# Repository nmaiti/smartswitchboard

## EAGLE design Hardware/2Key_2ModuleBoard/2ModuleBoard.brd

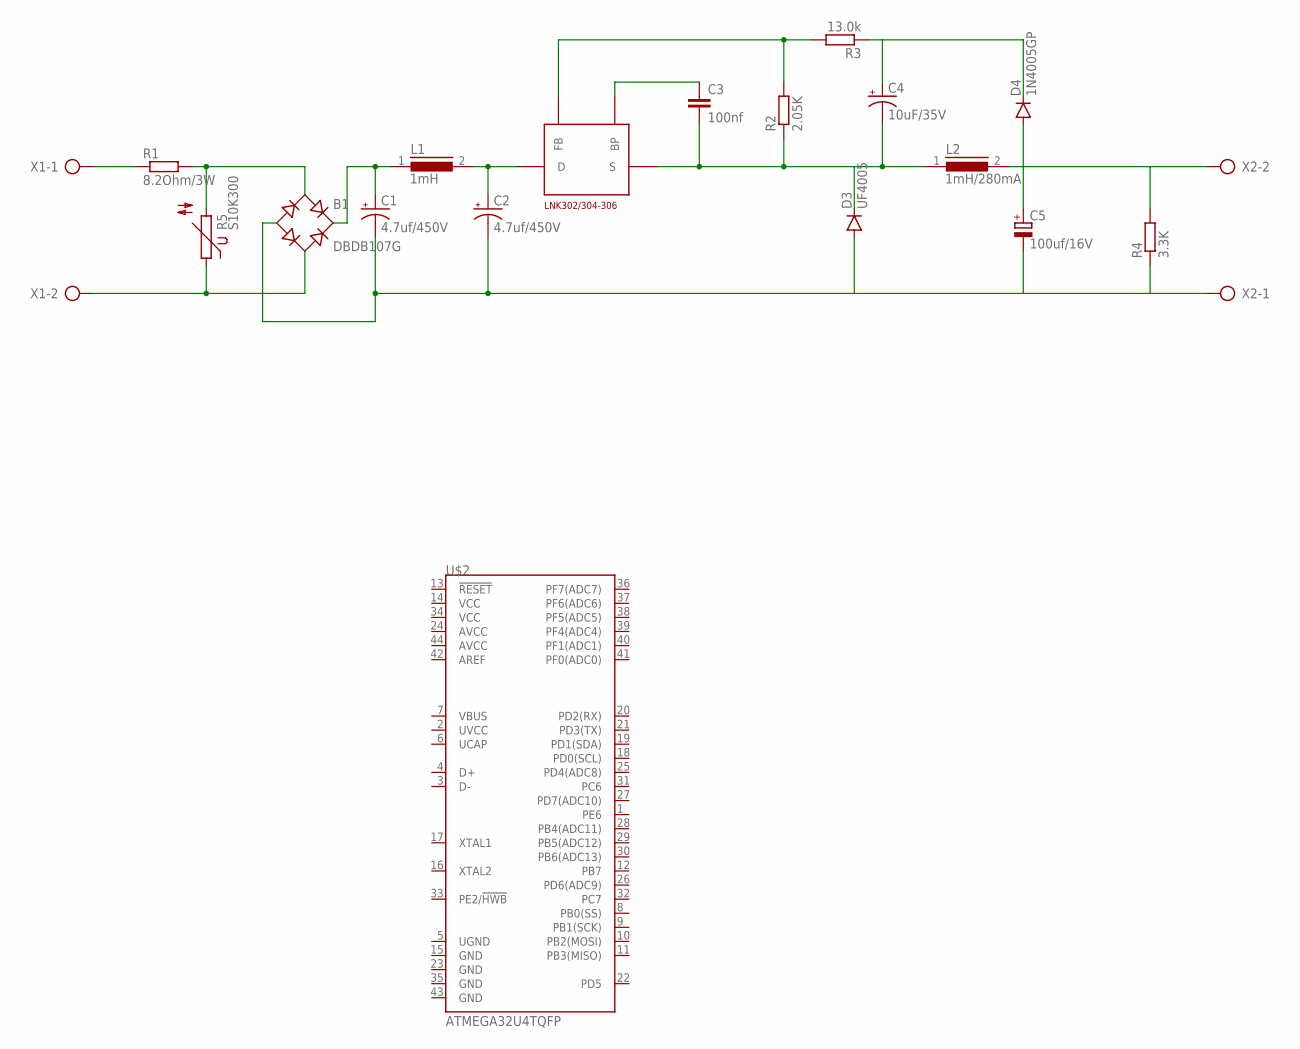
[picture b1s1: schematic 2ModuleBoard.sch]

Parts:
B1: DBDB107G; DB
C1, C2: 4.7uf/450V; CPOL-RADIAL-1000UF-25V-KIT
C3: 100nf; C2.5-4
C4: 10uF/35V; EIA3216
C5: 100uf/16V; E2,5-7
D3: UF4005; DIODE-1N4148-KIT
D4: 1N4005GP; DIODE-1N4148-KIT
L1: 1mH; 82114R
L2: 1mH/280mA; 82114R
R1: 8.2Ohm/3W; 0411/15
R2: 2.05K; M1206
R3: 13.0k; M1206
R4: 3.3K; M1206
R5: S10K300
U$1: LNK302/304-306; SMD-8B
U$2: ATMEGA32U4TQFP; SPARKFUN-DIGITALIC_TQFP44
X1, X2: AK300/2

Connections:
unnamed: R1.1, X1.1
unnamed: B1.AC1, R1.2, R5.2
unnamed: B1.+, C1.+, L1.1
unnamed: C2.+, L1.2, U$1.D
unnamed: B1.AC2, R5.1, X1.2
unnamed: B1.-, C1.-, C2.-, C5.-, D3.A, R4.1, X2.1
unnamed: C3.2, C4.C (-), D3.C, L2.1, R2.1, U$1.S1 (S)
unnamed: C3.1, U$1.BP
unnamed: R2.2, R3.2, U$1.FB
unnamed: C4.A (+), D4.C, R3.1
unnamed: C5.+, D4.A, L2.2, R4.2, X2.2

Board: 2 copper layers, 19 parts (0 on the bottom side), 11 nets, no tracks yet.

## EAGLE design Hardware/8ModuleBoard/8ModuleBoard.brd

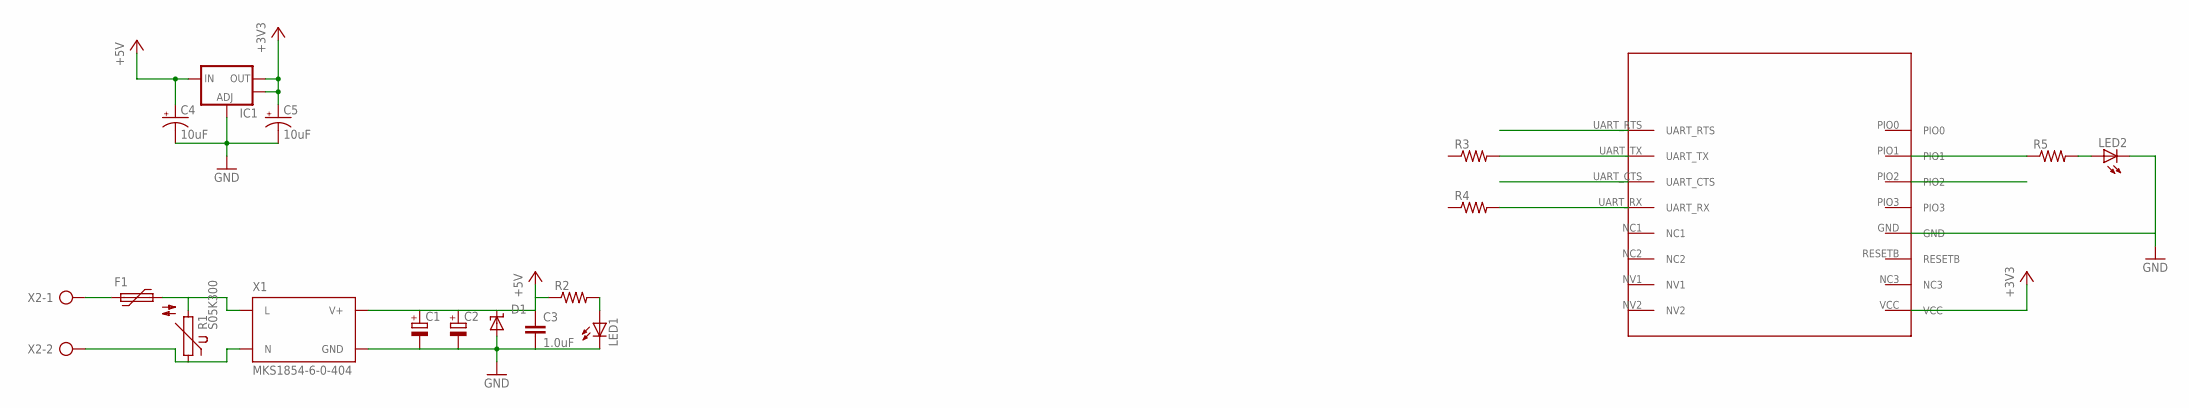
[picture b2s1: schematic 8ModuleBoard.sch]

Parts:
C1, C2: CPOL-EUE5-8.5; E5-8,5
C3: 1.0uF; 1206
C4, C5: 10uF; EIA3216
D1: SUPPRESSOR-SMBJ; SMBJ
F1: MF-R055-5,1B; MF-5,1B
IC1: V_REG_LM1117SOT223; SOT223
LED1, LED2: LEDSMT1206; 1206
R1: S05K300
R2, R3, R4, R5: RESISTOR1206; 1206
U$1: HM-11
X1: MKS1854-6-0-404
X2: AK300/2

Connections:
+3V3: C5.A (+), IC1.2 (OUT), IC1.4 (OUT)
+5V: C1.+, C2.+, C3.1, C4.A (+), D1.C, IC1.3 (IN), R2.1, X1.3 (V+)
GND: C1.-, C2.-, C3.2, C4.C (-), C5.C (-), D1.A, IC1.1 (ADJ), LED1.C, LED2.C, X1.4 (GND)
unnamed: F1.1, X2.1
unnamed: R1.1, X1.2 (N), X2.2
unnamed: F1.2, R1.2, X1.1 (L)
unnamed: R3.2, U$1.UART_TX
unnamed: R4.2, U$1.UART_RX
unnamed: LED2.A, R5.2
unnamed: LED1.A, R2.2

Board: 2 copper layers, 18 parts (0 on the bottom side), 10 nets, no tracks yet.

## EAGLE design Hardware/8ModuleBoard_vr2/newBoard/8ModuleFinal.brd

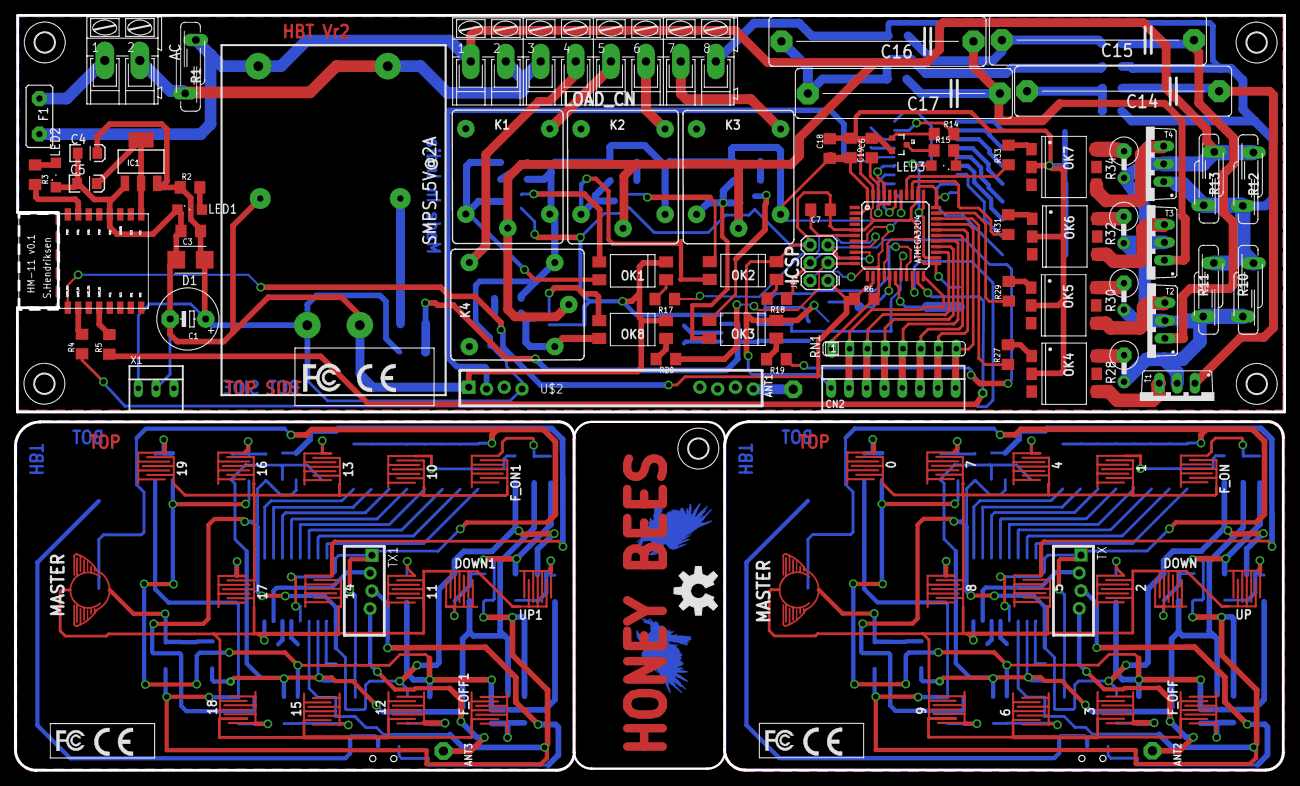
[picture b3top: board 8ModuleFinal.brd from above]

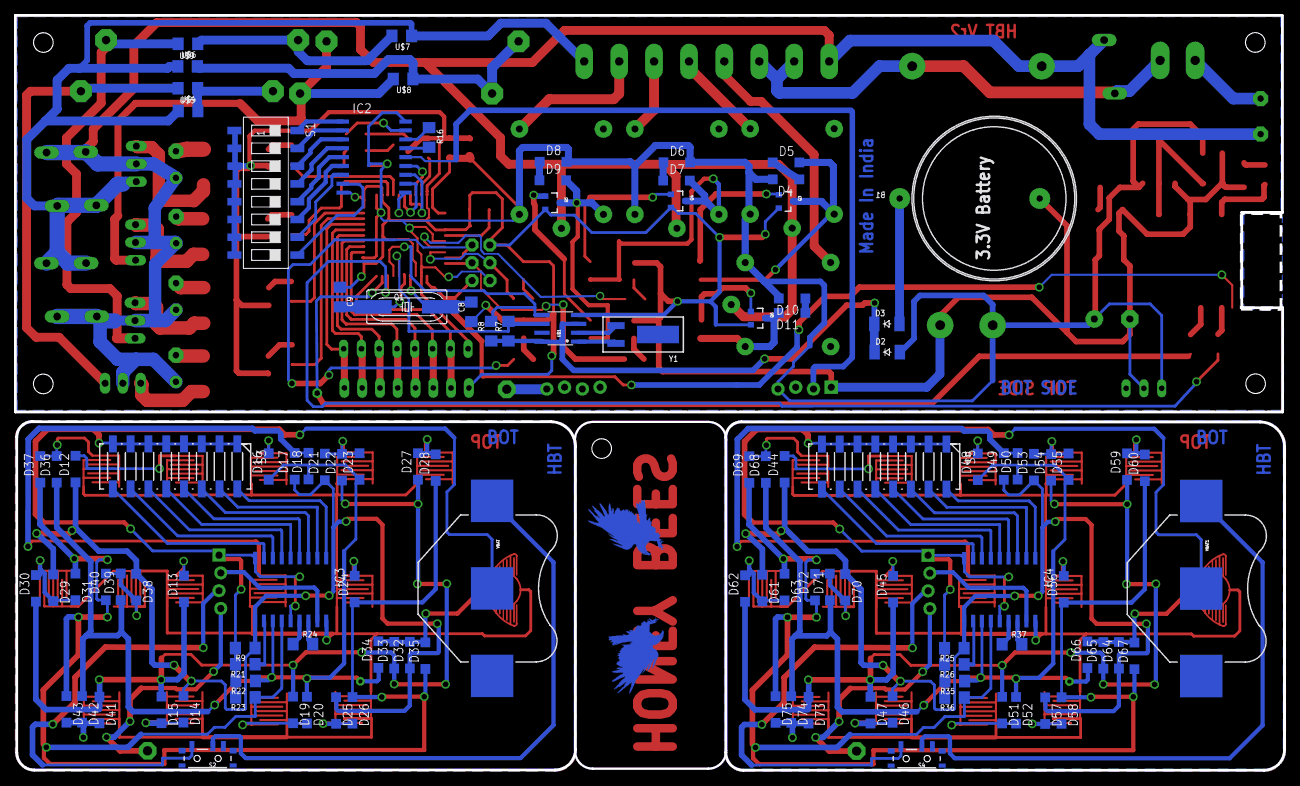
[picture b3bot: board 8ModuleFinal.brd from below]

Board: 2 copper layers, 181.3 x 107.8 mm, 231 parts (114 on the bottom side), 170 nets.

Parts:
0, 1, 2, 3, 4, 5, 6, 7, 8, 9, 10, 11, 12, 13, 14, 15, 16, 17, 18, 19: BUTTON-CONDUCTIVESMD; BUTTON-CONDUCTIVE
AC: AK300/2
ANT1, ANT2, ANT3: PAD-01
ATMEGA32U4: ATMEGA32U4TQFP-44; TQFP44
B1: CR2032
C1: 470uF/25V; E5-8,5
C3, C6, C18, C19: 0.1uF; 1206
C4, C5: 10uF; EIA3216
C7: 1uF; 1206
C8, C9: 18pF; 1206
C14, C16: 2.2uF/250VAC; C27.5B9
C15, C17: 3.3uF/250VAC; C27.5B9
CN2: Capsense I/P; 22-23-2081
D1: SMBJ
D2, D3: CGRM4007-G; SOD-123_MINI-SMA
D4, D5, D6, D7, D8, D9, D10, D11, D12, D13, D14, D15, D16, D17, D18, D19, D20, D21, D22, D23, D24, D25, D26, D27, D28, D29, D30, D31, D32, D33, D34, D35, D36, D37, D38, D39, D40, D41, D42, D43, D44, D45, D46, D47, D48, D49, D50, D51, D52, D53, D54, D55, D56, D57, D58, D59, D60, D61, D62, D63, D64, D65, D66, D67, D68, D69, D70, D71, D72, D73, D74, D75: SOD123
DOWN, DOWN1: BUTTON-CONDUCTIVESMD; BUTTON-CONDUCTIVE
E$1, E$2: EAGLE-TOP-8MM
E$3: 2,8
E$4: OSHW-LOGO-L
F1: PFUSE 1A; MF-5,1B
F_OFF, F_OFF1: BUTTON-CONDUCTIVESMD; BUTTON-CONDUCTIVE
F_ON, F_ON1: BUTTON-CONDUCTIVESMD; BUTTON-CONDUCTIVE
H1, H2, H3, H4: MOUNT-HOLE2.8; 2,8
IC1: SOT223
IC2, IC3, IC4: HT680D; SOP18
JP1: AVR_SPI_PRG_6PTH; 2X3
K1, K2, K3, K4: JS-M1-9V-4; JS-M
LED1, LED2, LED3: SML1206
LOAD_CN: AK300/8
MASTER, MASTER1: BUTTON-CONDUCTIVE; BUTTON-CONDUCTIVE-MINI
OK1, OK2, OK3, OK8: PC817DIL4; DIL4-SMD
OK4, OK5, OK6, OK7: MOC3031S; DIL6-SMD
Q1: 16MHz; HC49UP
Q2, Q3, Q4, Q5, Q6: MMBT2222A; SOT23-3
R1: MOV300V; S10K11
R2, R3, R4, R5, R9, R17, R18, R19, R20, R21, R22, R23, R25, R26, R35, R36: 1K; 1206
R6, R14: 10K; 1206
R7, R8: 4k7; 1206
R10, R11, R12, R13: S10K11
R15, R27, R29, R31, R33: 560R; 1206
R16: 33k; 1206
R24, R37: 750K; 1206
R28, R30, R32, R34: 470R/0.5W; 0411V
RN1: SIL8
S1: SWS008; SMS-008
S2, S4: SWITCH-SPST-SMD-A
S3, S5: 219-08J; CTS-219-08J
SMPS_5V@2A: 5V@2A; MKS1854-6-0-404
T1, T2, T3, T4: BTB16-V; TO220BV
TX, TX1: RF-LINK_TX
U$1: DS1307SO8; SO08
U$2: RF-LINK_RX
U$3: HM-11
U$4, U$6, U$8: 220K; 1206
U$5, U$7, U$9: 2E2; 1206
U$10, U$13, U$14: CE-4MM
U$11, U$15: FCC_6.1X15MM
U$12: FCC_20X8.35MM
UP, UP1: BUTTON-CONDUCTIVESMD; BUTTON-CONDUCTIVE
VBAT, VBAT1: BATTCON_20MM
X1: 22-23-2031
Y1: 32.768KHz; CRYSTAL_CYL_2X6MM_SMT

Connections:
!RESET: ATMEGA32U4.13, JP1.1, R6.1, U$3.UART_RTS
(DIN)TE: IC2.14, U$2.DATA@1
(VT)ADOUT: IC2.17, R14.2
+3V3: C5.A, IC1.2, IC1.4, U$3.VCC
+5V: ATMEGA32U4.2, ATMEGA32U4.7, ATMEGA32U4.14, ATMEGA32U4.24, ATMEGA32U4.34, ATMEGA32U4.44, C1.+, C3.1, C4.A, C18.1, C19.2, D1.C, D2.A, D4.A, D6.A, D8.A, D10.A, IC1.3, IC2.18, JP1.2, K1.1, K2.1, K3.1, K4.1, LED3.A, R2.1, R6.2, RN1.1, SMPS_5V@2A.3, U$2.+5V@1, X1.1
A0: IC2.1, S1.16
A1: IC2.2, S1.15
A2: IC2.3, S1.14
A3: IC2.4, S1.13
A4: IC2.5, S1.12
A5: IC2.6, S1.11
A6: IC2.7, S1.10
A7: IC2.8, S1.9
BLE_STATUS: R3.2, U$3.PIO1
D8: ATMEGA32U4.38, IC2.10
D9: ATMEGA32U4.39, IC2.11
D10: ATMEGA32U4.40, IC2.12
D11: ATMEGA32U4.41, IC2.13
DOWN: ATMEGA32U4.29, CN2.7, RN1.7
EA0: IC3.1, S3.16
EA1: IC3.2, S3.15
EA2: IC3.3, S3.14
EA3: IC3.4, S3.13
EA4: IC3.5, S3.12
EA5: IC3.6, S3.11
EA6: IC3.7, S3.10
EA7: IC3.8, S3.9
EA8: IC4.1, S5.16
EA9: IC4.2, S5.15
EA10: IC4.3, S5.14
EA11: IC4.4, S5.13
EA12: IC4.5, S5.12
EA13: IC4.6, S5.11
EA14: IC4.7, S5.10
EA15: IC4.8, S5.9
EAD1: D44.C, D46.C, D49.C, D53.C, D57.C, D61.C, D64.C, D70.C, IC4.10, R25.1
EAD2: IC4.11, R26.1
EAD3: D48.C, D50.C, D52.C, D55.C, D66.C, D68.C, D71.C, D74.C, IC4.12, R35.1
EAD4: D56.C, D58.C, D60.C, D63.C, D67.C, D69.C, D72.C, D75.C, IC4.13, R36.1
EAD8: D12.C, D14.C, D17.C, D21.C, D25.C, D29.C, D32.C, D38.C, IC3.10, R9.1
EAD9: IC3.11, R21.1
EAD10: D16.C, D18.C, D20.C, D23.C, D34.C, D36.C, D39.C, D42.C, IC3.12, R22.1
EAD11: D24.C, D26.C, D28.C, D31.C, D35.C, D37.C, D40.C, D43.C, IC3.13, R23.1
EDOUT: IC3.17, TX.DATA
EDOUT1: IC4.17, TX1.DATA
EOSC1: IC3.16, R24.2
EOSC2: IC3.15, R24.1
EOSC3: IC4.15, R37.1
EOSC4: IC4.16, R37.2
FAN_ON/OFF: ATMEGA32U4.30, CN2.8, RN1.8
FAN_REG: LOAD_CN.8, R10.1, R11.1, R12.1, R13.1, T4.T1, U$5.1, U$7.1, U$9.1
GND: ATMEGA32U4.5, ATMEGA32U4.15, ATMEGA32U4.23, ATMEGA32U4.33, ATMEGA32U4.35, ATMEGA32U4.43, B1.-, C1.-, C3.2, C4.C, C5.C, C6.2, C7.1, C8.1, C9.1, C18.2, C19.1, CN2.1, D1.A, IC1.1, IC2.9, JP1.6, LED1.C, LED2.C, OK1.2, OK2.2, OK3.2, OK4.2, OK5.2, OK6.2, OK7.2, OK8.2, Q2.2, Q3.2, Q4.2, Q5.2, Q6.2, S1.1, S1.2, S1.3, S1.4, S1.5, S1.6, S1.7, S1.8, SMPS_5V@2A.4, U$1.4, U$2.GND@1, U$3.GND, X1.2
GNDA: IC3.9, IC3.14, R9.2, R21.2, R22.2, R23.2, S3.1, S3.2, S3.3, S3.4, S3.5, S3.6, S3.7, S3.8, TX.GND, VBAT.2
GNDA1: IC4.9, IC4.14, R25.2, R26.2, R35.2, R36.2, S5.1, S5.2, S5.3, S5.4, S5.5, S5.6, S5.7, S5.8, TX1.GND, VBAT1.2
LEVEL1: ATMEGA32U4.31, R27.1
LEVEL2: ATMEGA32U4.32, R29.1
LEVEL3: ATMEGA32U4.36, R31.1
LEVEL4: ATMEGA32U4.37, R33.1
LINE: F1.1, K1.C, K2.C, K3.C, K4.C, LOAD_CN.1, R1.2, R10.2, R11.2, R12.2, R13.2, R28.2, R30.2, R32.2, R34.2, SMPS_5V@2A.1, T1.T2, T2.T2, T3.T2, T4.T2
LOAD_1: K4.NO, LOAD_CN.4
LOAD_2: K1.NO, LOAD_CN.5
LOAD_3: K2.NO, LOAD_CN.6
MISO: ATMEGA32U4.11, JP1.3, R20.1
MOSI: ATMEGA32U4.10, JP1.5, R19.1
unnamed: OK6.1, R31.2
unnamed: OK4.1, R27.2
unnamed: OK5.1, R29.2
unnamed: OK4.6, R28.1
unnamed: OK7.1, R33.2
unnamed: R4.2, U$3.UART_TX
unnamed: ATMEGA32U4.6, C7.2
unnamed: Q2.1, R14.1
unnamed: LED2.A, R3.1
unnamed: ATMEGA32U4.42, C6.1
unnamed: R5.2, U$3.UART_RX
unnamed: U$1.1, Y1.1
unnamed: U$1.2, Y1.2
unnamed: D2.C, D3.C, R7.1, R8.1, U$1.3, U$1.8
unnamed: LED1.A, R2.2
unnamed: B1.+, D3.A
unnamed: 1.2, D12.A
unnamed: 2.2, D13.A
unnamed: ATMEGA32U4.16, C8.2, Q1.2
unnamed: ATMEGA32U4.17, C9.2, Q1.1
unnamed: Q2.3, R15.1
unnamed: S2.2, VBAT.1
unnamed: LED3.C, R15.2
unnamed: S2.3, TX.VCC
unnamed: OK5.6, R30.1
unnamed: OK6.6, R32.1
unnamed: ANT1.1, U$2.ANT
unnamed: OK1.3, Q3.1
unnamed: D5.A, K1.2, OK1.4, Q3.3
unnamed: OK7.6, R34.1
unnamed: 3.2, D14.A, D15.A
unnamed: AC.1, F1.2
unnamed: D4.C, D5.C
unnamed: ANT2.1, TX.ANT
unnamed: OK1.1, R17.2
unnamed: 4.2, D16.A
unnamed: OK2.3, Q4.1
unnamed: 5.2, D17.A, D18.A
unnamed: D7.A, K2.2, OK2.4, Q4.3
unnamed: D6.C, D7.C
unnamed: 6.2, D19.A, D20.A
unnamed: 7.2, D21.A, D22.A, D23.A
unnamed: OK2.1, R18.2
unnamed: OK3.3, Q5.1
unnamed: 0.2, D27.A, D28.A
unnamed: D9.A, K3.2, OK3.4, Q5.3
unnamed: OK4.4, T1.G
unnamed: C14.1, T1.T1, U$4.2
unnamed: C14.2, U$4.1, U$5.2
unnamed: D8.C, D9.C
unnamed: D13.C, D15.C, D19.C, D22.C, D27.C, D30.C, D33.C, D41.C
unnamed: D29.A, D30.A, D31.A, UP.2
unnamed: 8.2, D24.A
unnamed: OK5.4, T2.G
unnamed: C15.1, T2.T1, U$6.2
unnamed: C15.2, U$6.1, U$7.2
unnamed: OK3.1, R19.2
unnamed: OK8.3, Q6.1
unnamed: D11.A, K4.2, OK8.4, Q6.3
unnamed: D36.A, D37.A, F_ON.2
unnamed: D10.C, D11.C
unnamed: OK6.4, T3.G
unnamed: C16.1, C17.1, T3.T1, U$8.2
unnamed: C16.2, C17.2, U$8.1, U$9.2
unnamed: 9.2, D25.A, D26.A
unnamed: D38.A, D39.A, D40.A, DOWN.2
unnamed: D32.A, D33.A, D34.A, D35.A, MASTER.2
unnamed: OK8.1, R20.2
unnamed: OK7.4, T4.G
unnamed: D41.A, D42.A, D43.A, F_OFF.2
unnamed: S4.2, VBAT1.1
unnamed: S4.3, TX1.VCC
unnamed: ATMEGA32U4.8, R17.1
unnamed: ANT3.1, TX1.ANT
unnamed: 10.2, D44.A
unnamed: 11.2, D45.A
unnamed: 12.2, D46.A, D47.A
unnamed: 13.2, D48.A
unnamed: 14.2, D49.A, D50.A
unnamed: 15.2, D51.A, D52.A
unnamed: D45.C, D47.C, D51.C, D54.C, D59.C, D62.C, D65.C, D73.C
unnamed: 16.2, D53.A, D54.A, D55.A
unnamed: 17.2, D56.A
unnamed: 18.2, D57.A, D58.A
unnamed: 19.2, D59.A, D60.A
unnamed: D64.A, D65.A, D66.A, D67.A, MASTER1.2
unnamed: D61.A, D62.A, D63.A, UP1.2
unnamed: D68.A, D69.A, F_ON1.2
unnamed: D70.A, D71.A, D72.A, DOWN1.2
unnamed: D73.A, D74.A, D75.A, F_OFF1.2
NEUTRAL: AC.2, LOAD_CN.2, LOAD_CN.3, R1.1, SMPS_5V@2A.2
OSC1: IC2.16, R16.1
OSC2: IC2.15, R16.2
PLUG_CONTROL: K3.NO, LOAD_CN.7
RX: ATMEGA32U4.21, R5.1
SCK: ATMEGA32U4.9, JP1.4, R18.1
SCL: ATMEGA32U4.18, R7.2, U$1.6
SDA: ATMEGA32U4.19, R8.2, U$1.5
SW-1: ATMEGA32U4.22, CN2.2, RN1.2
SW-2: ATMEGA32U4.25, CN2.3, RN1.3
SW-3: ATMEGA32U4.26, CN2.4, RN1.4
SW-4: ATMEGA32U4.27, CN2.5, RN1.5
TX: ATMEGA32U4.20, R4.1
UP: ATMEGA32U4.28, CN2.6, RN1.6
V+: 0.1, 1.1, 2.1, 3.1, 4.1, 5.1, 6.1, 7.1, 8.1, 9.1, DOWN.1, F_OFF.1, F_ON.1, IC3.18, MASTER.1, UP.1
V+1: 10.1, 11.1, 12.1, 13.1, 14.1, 15.1, 16.1, 17.1, 18.1, 19.1, DOWN1.1, F_OFF1.1, F_ON1.1, IC4.18, MASTER1.1, UP1.1

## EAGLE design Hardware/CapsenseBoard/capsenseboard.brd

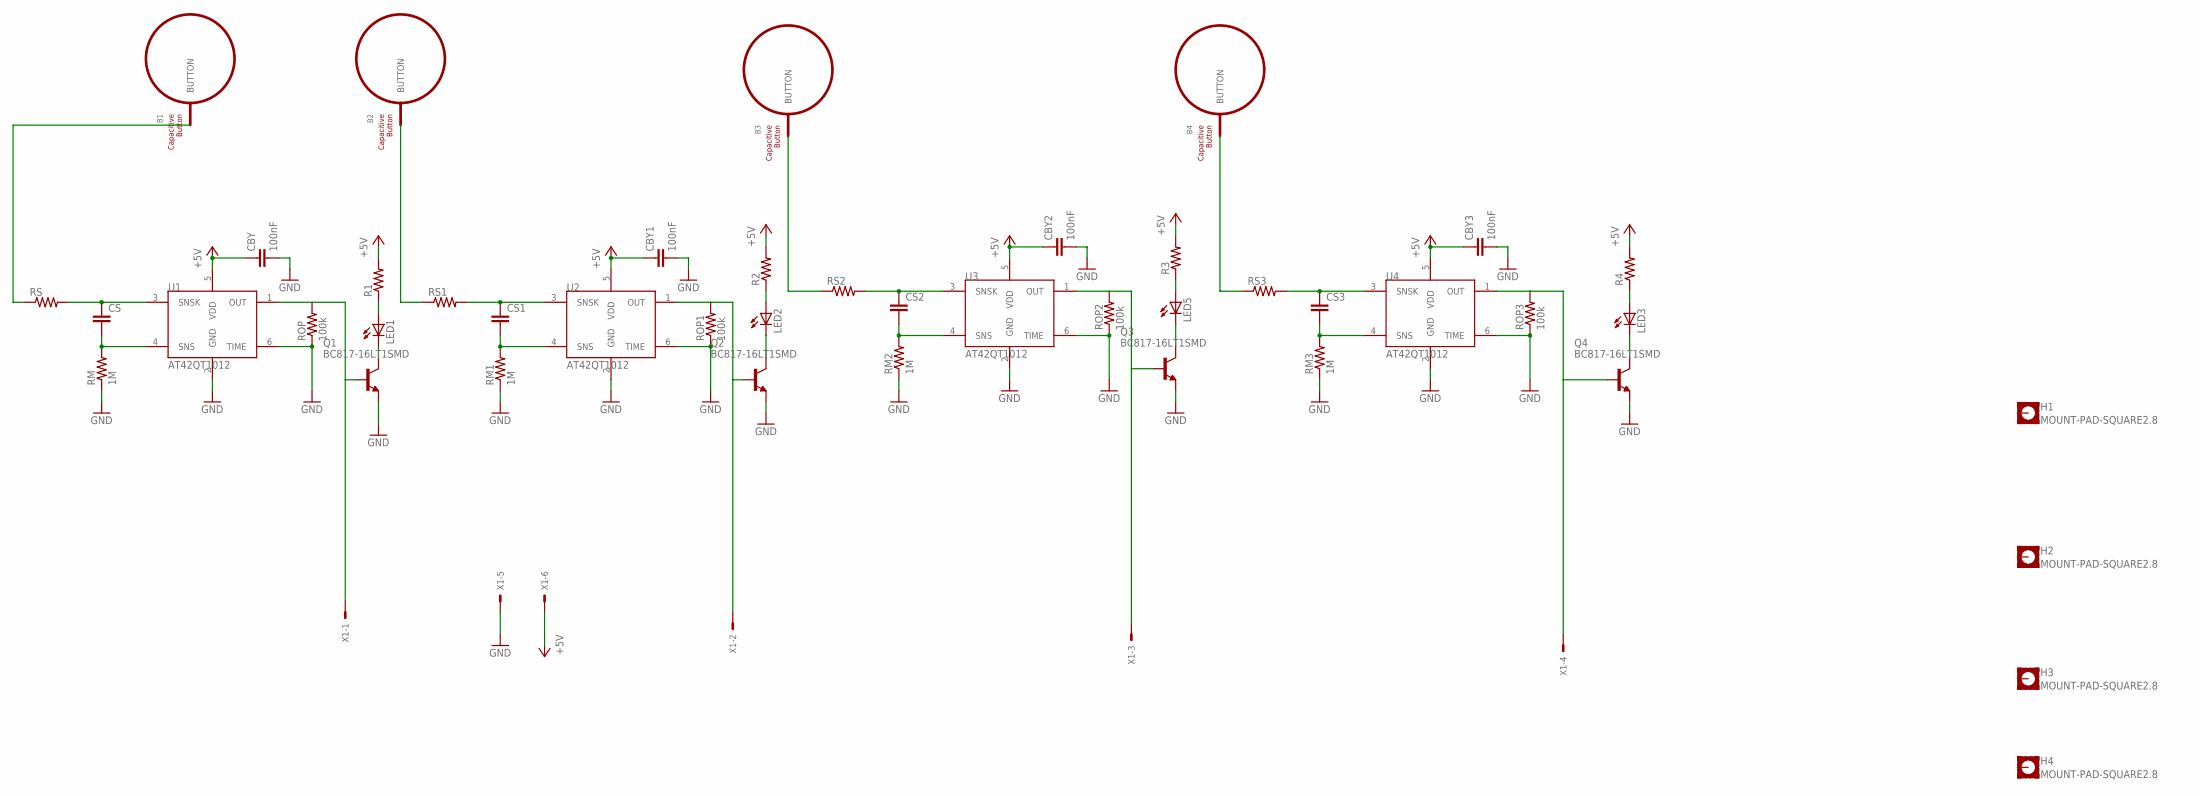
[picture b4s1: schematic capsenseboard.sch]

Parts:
B1, B2, B3, B4: BUTTON_PASSIVE12MM; BUTTON_PASSIVE_12MM
CBY, CBY1, CBY2, CBY3: 100nF; C1206K
CS, CS1, CS2, CS3: C-EUC1206K; C1206K
H1, H2, H3, H4: MOUNT-PAD-SQUARE2.8; 2,8-PAD-SQUARE
LED1, LED2, LED3, LED5: LEDCHIPLED_1206; CHIPLED_1206
Q1, Q2, Q3, Q4: BC817-16LT1SMD; SOT23-BEC
R1, R2, R3, R4: R-US_R1206; R1206
RM, RM1, RM2, RM3: 1M; R1206
ROP, ROP1, ROP2, ROP3: 100k; R1206
RS, RS1, RS2, RS3: R-US_R1206; R1206
U1, U2, U3, U4: AT42QT1012; SOT-23-6
X1: 22-23-2061

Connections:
+5V: CBY.1, CBY1.1, CBY2.1, CBY3.1, R1.2, R2.2, R3.2, R4.2, U1.5 (VDD), U2.5 (VDD), U3.5 (VDD), U4.5 (VDD), X1.6
GND: CBY.2, CBY1.2, CBY2.2, CBY3.2, Q1.E, Q2.E, Q3.E, Q4.E, RM.1, RM1.1, RM2.1, RM3.1, ROP.1, ROP1.1, ROP2.1, ROP3.1, U1.2 (GND), U1.6 (TIME), U2.2 (GND), U2.6 (TIME), U3.2 (GND), U3.6 (TIME), U4.2 (GND), U4.6 (TIME), X1.5
unnamed: CS.1, RS.2, U1.3 (SNSK)
unnamed: CS.2, RM.2, U1.4 (SNS)
unnamed: Q1.B, ROP.2, U1.1 (OUT), X1.1
unnamed: B1.BUTTON, RS.1
unnamed: CS1.1, RS1.2, U2.3 (SNSK)
unnamed: CS1.2, RM1.2, U2.4 (SNS)
unnamed: Q2.B, ROP1.2, U2.1 (OUT), X1.2
unnamed: B2.BUTTON, RS1.1
unnamed: CS2.1, RS2.2, U3.3 (SNSK)
unnamed: CS2.2, RM2.2, U3.4 (SNS)
unnamed: Q4.B, ROP3.2, U4.1 (OUT), X1.4
unnamed: B3.BUTTON, RS2.1
unnamed: CS3.1, RS3.2, U4.3 (SNSK)
unnamed: CS3.2, RM3.2, U4.4 (SNS)
unnamed: B4.BUTTON, RS3.1
unnamed: LED1.A, R1.1
unnamed: LED1.C, Q1.C
unnamed: Q3.B, ROP2.2, U3.1 (OUT), X1.3
unnamed: LED5.A, R3.1
unnamed: LED2.A, R2.1
unnamed: LED2.C, Q2.C
unnamed: LED5.C, Q3.C
unnamed: LED3.A, R4.1
unnamed: LED3.C, Q4.C

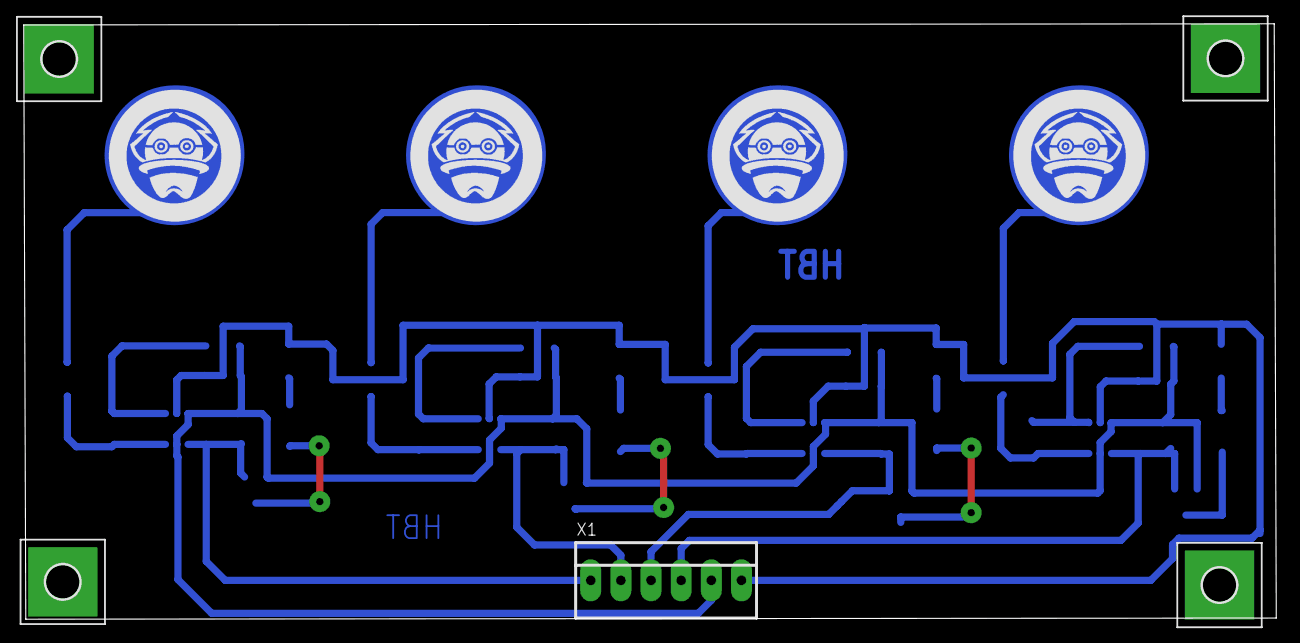
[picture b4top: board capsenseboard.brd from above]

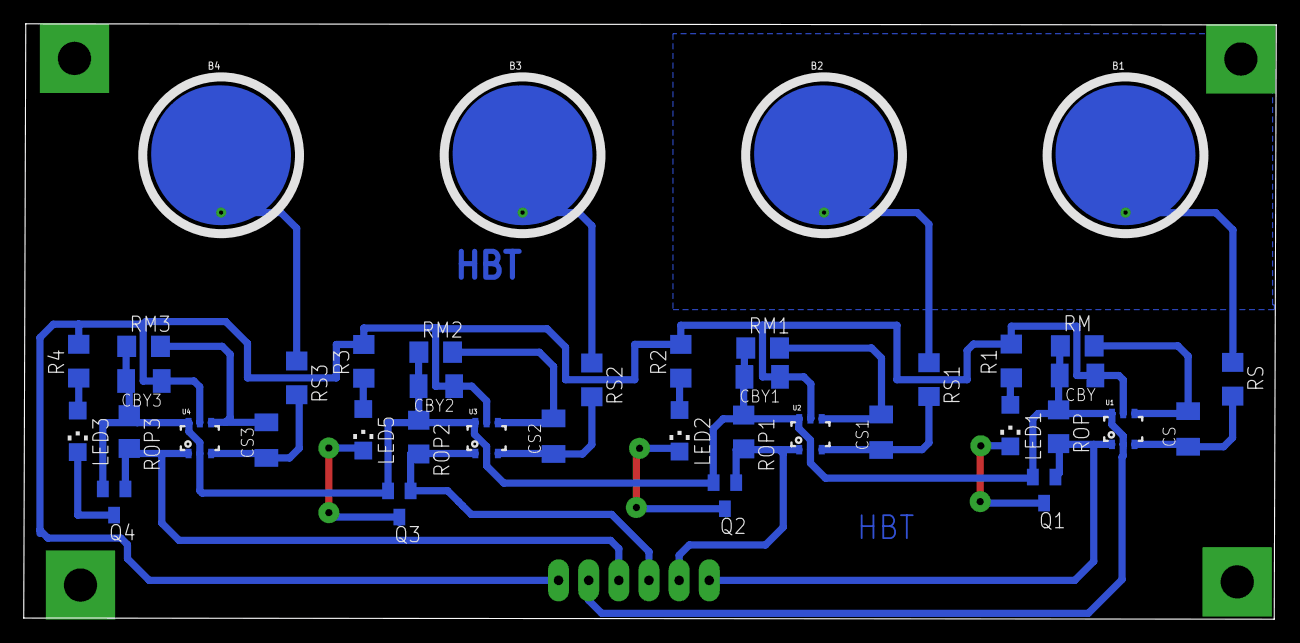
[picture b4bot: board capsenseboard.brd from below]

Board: 2 copper layers, 105.5 x 50.2 mm, 45 parts (40 on the bottom side), 26 nets.

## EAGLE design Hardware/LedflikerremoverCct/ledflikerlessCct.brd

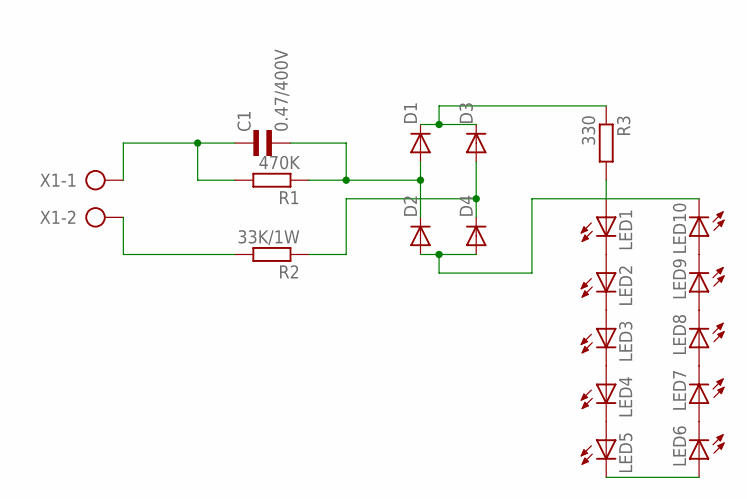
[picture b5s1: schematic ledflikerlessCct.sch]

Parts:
C1: 0.47/400V; EU25-10
D1, D2, D3, D4: DIODE-D-5; D-5
LED1, LED2, LED3, LED4, LED5, LED6, LED7, LED8, LED9, LED10: LEDP-LCC-2-BACK; P-LCC-2-TOPLED-RG
R1: 470K; 0207/10
R2: 33K/1W; 0411/15
R3: 330; R1206
X1: AK300/2

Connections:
unnamed: D1.C, D3.C, R3.1
unnamed: C1.2, D1.A, D2.C, R1.1
unnamed: D3.A, D4.C, R2.1
unnamed: LED1.C, LED2.A
unnamed: C1.1, R1.2, X1.1
unnamed: LED2.C, LED3.A
unnamed: R2.2, X1.2
unnamed: LED1.A, R3.2
unnamed: D2.A, D4.A, LED10.C
unnamed: LED3.C, LED4.A
unnamed: LED4.C, LED5.A
unnamed: LED6.C, LED7.A
unnamed: LED7.C, LED8.A
unnamed: LED8.C, LED9.A
unnamed: LED9.C, LED10.A
unnamed: LED5.C, LED6.A

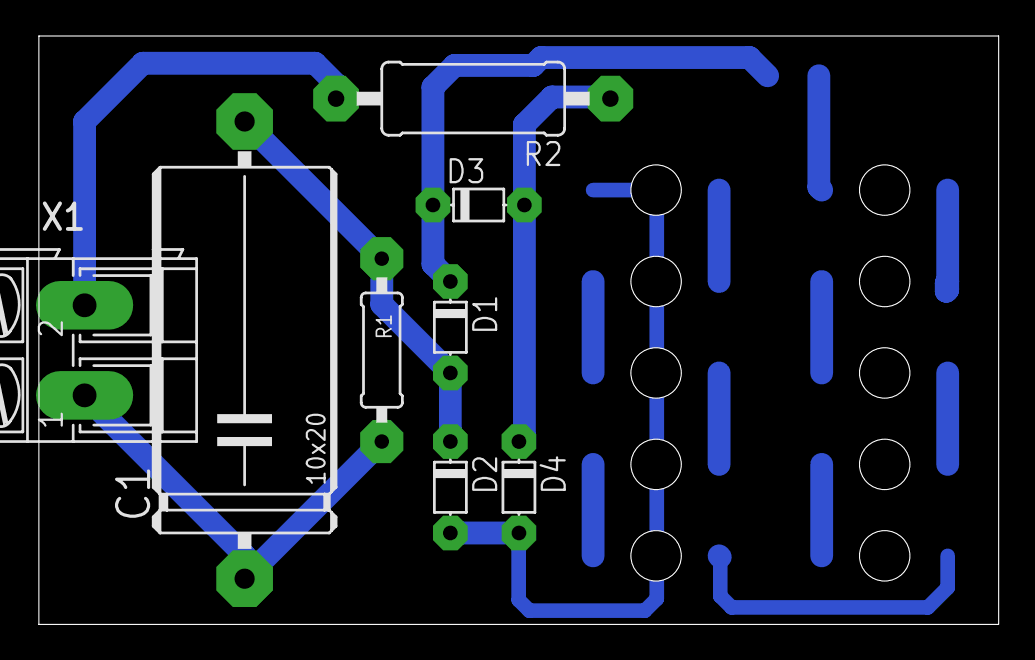
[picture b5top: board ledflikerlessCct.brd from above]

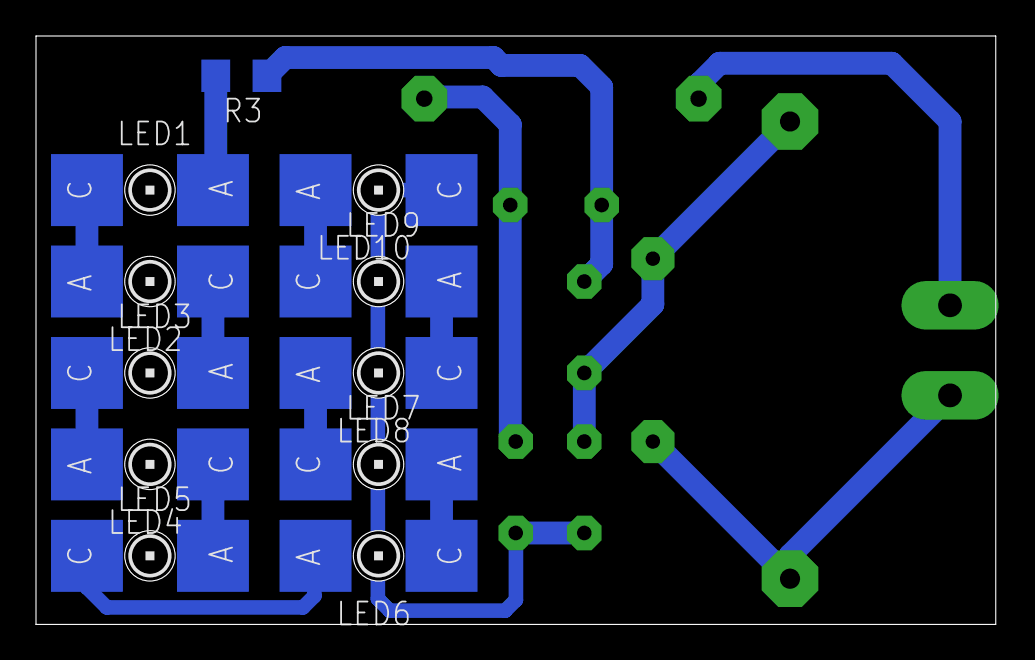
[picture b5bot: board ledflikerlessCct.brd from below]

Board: 2 copper layers, 53.3 x 32.7 mm, 19 parts (11 on the bottom side), 16 nets.

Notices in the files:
parts and their libraries:
SparkFun-DiscreteSemi: Licensing: Creative Commons ShareAlike 4.0 International - https://creativecommons.org/licenses/by-sa/4.0
microbuilder: This work is placed in the public domain, and may be freely used for commercial and non-commercial work with the following conditions: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
